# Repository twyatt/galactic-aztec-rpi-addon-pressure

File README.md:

# About

Custom Raspberry Pi Add-on board used as a pressure transducer interface board for the [Galactic Aztec] rocket. The board has a single JST XH port for power input (Supply Voltage), 4 ethernet ports for interfacing with custom [pressure transducer connector boards] and 2 header pin ports (pressure transducer stepped-down voltage output) for optional ribbon cable connectivity.

## Wiring
The ethernet ports adhere to the following [T-568B] wiring configuration:

| Pin | Color        | Function       |
|:---:|:------------:|:--------------:|
| 1   | Orange/White | Signal         |
| 2   | Orange       | Signal         |
| 3   | Green/White  |                |
| 4   | Blue         | Supply Voltage |
| 5   | Blue/White   | Supply Voltage |
| 6   | Green        |                |
| 7   | Brown/White  | Ground         |
| 8   | Brown        | Ground         |

## Launch
For the [Galactic Aztec April 18th, 2015 launch], the following pressure transducers were used:
* 3 x [P51-500-A-A-I36-5V-000-000]
  * LOX, Kerosene and motor pressure
* 1 x [MSP-300-2K5-P-4-N-1]
  * Helium pressure

Custom EagleCAD parts on this board can be found in the [SDSU Rocket Eagle Libraries].

# Bill of Materials
| Qty | Description                               | Part Number       | Vendor   |
|:---:|-------------------------------------------|------------------:|----------|
| 4   | Jack RJ45 CAT5/CAT5e                      | [380-1046-ND]     | DigiKey  |
| 1   | Header JST XH 2.5mm 4-pos Right Angle SMD | [455-2262-1-ND]   | DigiKey  |
| 2   | Header Male 2x5 0.1" Pitch                | [609-3236-ND]     | DigiKey  |
| 4   | Resistor 10kΩ 1/4W 1% 0603                | [P10KBYCT-ND]     | DigiKey  |
| 4   | Resistor 15kΩ 1/4W 1% 0603                | [RHM15.0KADCT-ND] | DigiKey  |
| 1   | Header Stacking 2x20 Tall 23mm            | [1979]            | Adafruit |

[Galactic Aztec]: http://rocket.sdsu.edu/rockets
[pressure transducer connector boards]: https://github.com/twyatt/galactic-aztec-pressure-transducer-connector
[T-568B]: https://en.wikipedia.org/wiki/TIA/EIA-568#Wiring
[Galactic Aztec April 18th, 2015 launch]: https://github.com/twyatt/galactic-aztec-launch-data
[P51-500-A-A-I36-5V-000-000]: http://www.ssi-sensors.com/pdfs/Pressure%20Sensors/P51/PS-AN2_FAMILY%20PRODUCT%20OVERVIEW.pdf
[MSP-300-2K5-P-4-N-1]: http://www.mouser.com/ds/2/418/MSP300-710393.pdf
[SDSU Rocket Eagle Libraries]: https://github.com/twyatt/SDSURocket-Eagle-Libraries
[380-1046-ND]: http://www.digikey.com/product-detail/en/SS-7188-NF/380-1046-ND/388308
[455-2262-1-ND]: http://www.digikey.com/product-detail/en/S4B-XH-SM4-TB(LF)(SN)/455-2262-1-ND/1651060
[609-3236-ND]: http://www.digikey.com/product-detail/en/67997-210HLF/609-3236-ND/1878541
[P10KBYCT-ND]: http://www.digikey.com/product-detail/en/ERJ-PA3F1002V/P10KBYCT-ND/5036115
[RHM15.0KADCT-ND]: http://www.digikey.com/product-detail/en/ESR03EZPF1502/RHM15.0KADCT-ND/1983758
[1979]: https://www.adafruit.com/product/1979

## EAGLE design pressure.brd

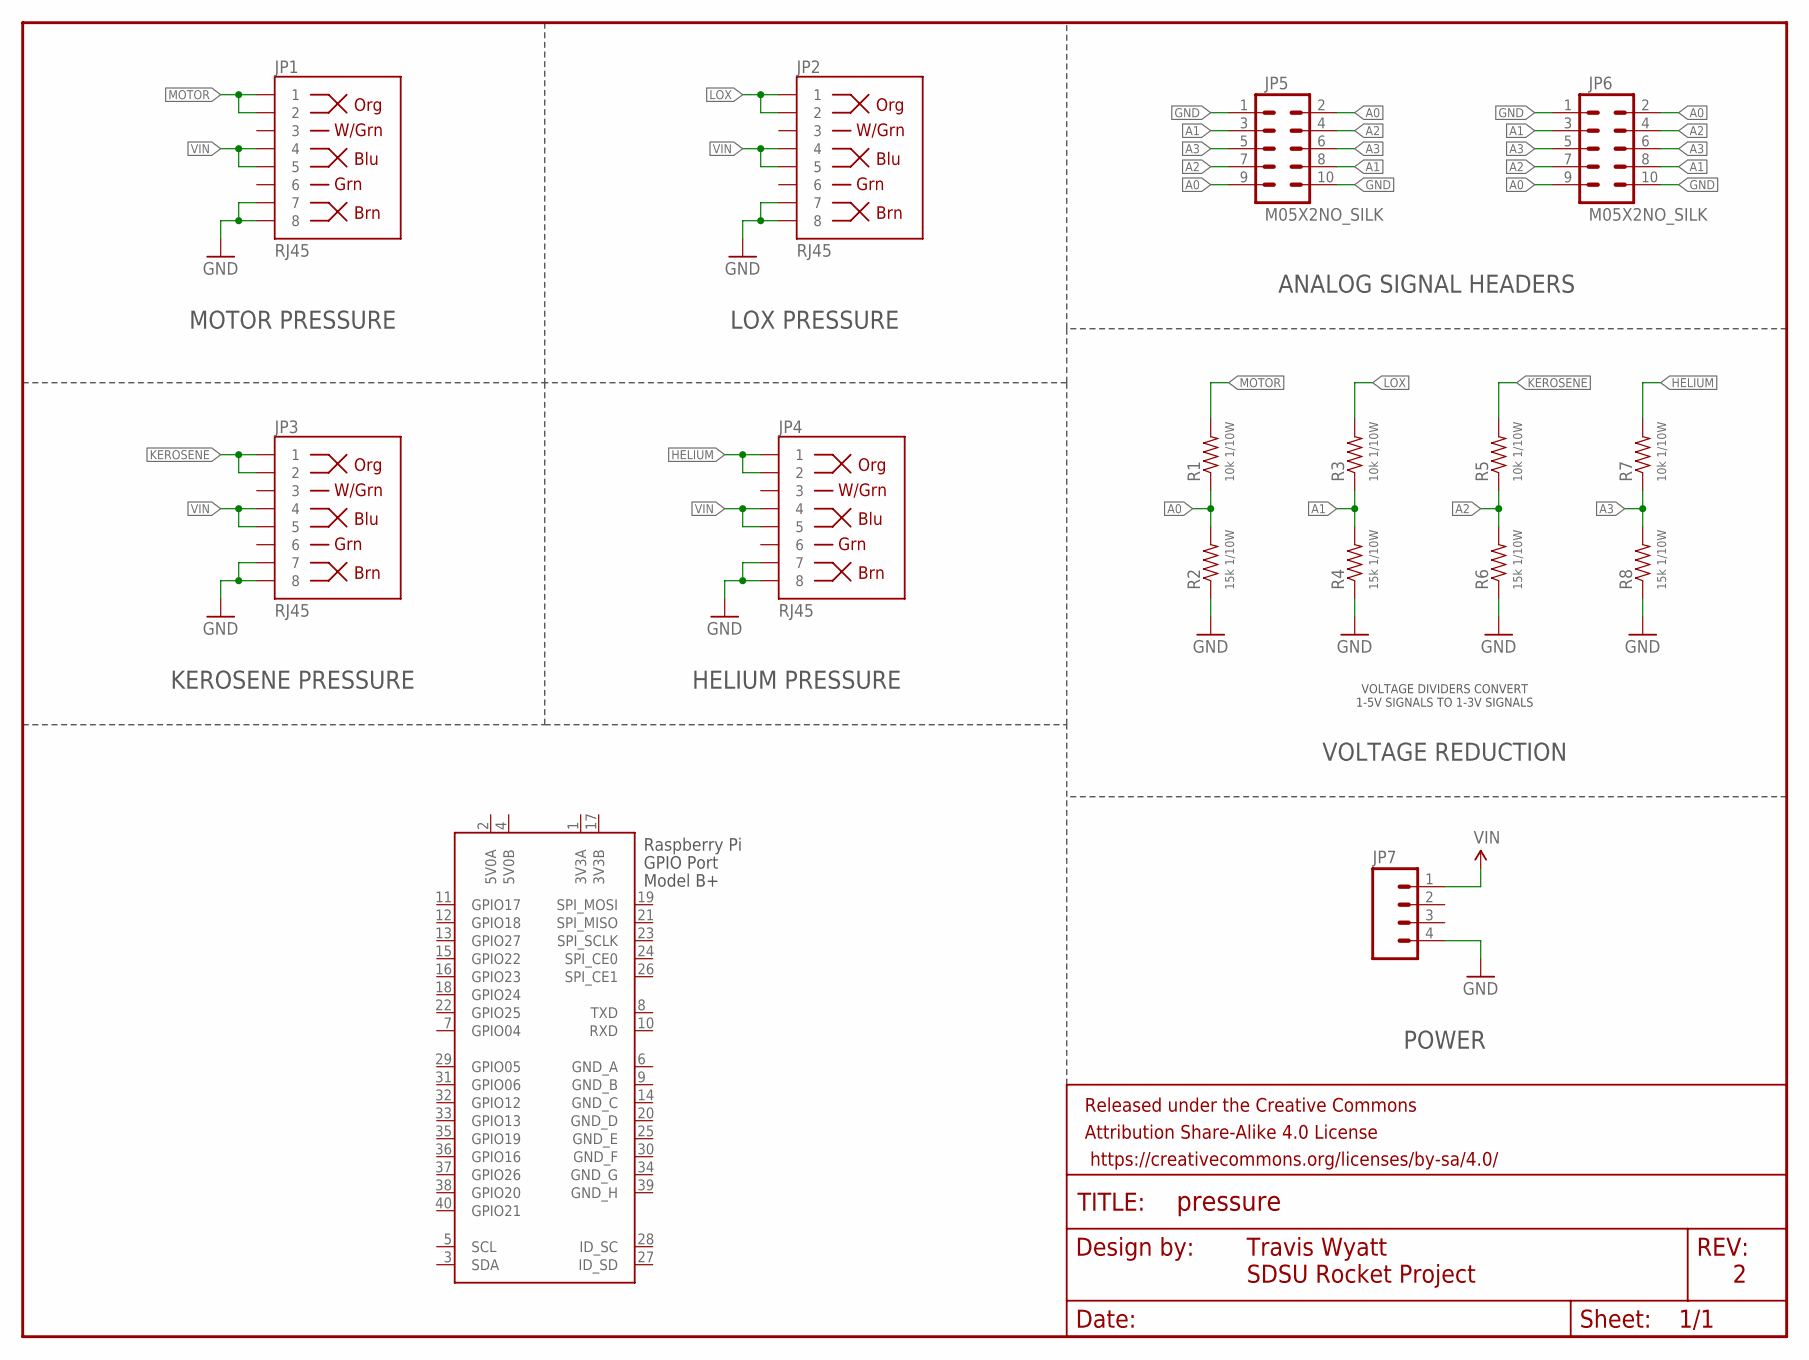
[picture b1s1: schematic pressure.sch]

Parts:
FRAME1: FRAME-LETTER; CREATIVE_COMMONS
JP1, JP2, JP3, JP4: RJ45; RJ45-8
JP5, JP6: M05X2NO_SILK; 2X5_NOSILK
JP7: JST-4POS-2.5MM; S4B-XH-SM4-TB
R1, R3, R5, R7: 10k 1/10W; 0603-RES
R2, R4, R6, R8: 15k 1/10W; 0603-RES
X1: RASPI_BOARD_B+#_H; RASPI_BOARD_B+HAT

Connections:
3V3A: X1.1 (3V3A)
3V3B: X1.17 (3V3B)
5V0A: X1.2 (5V0A)
5V0B: X1.4 (5V0B)
A0: JP5.2, JP5.9, JP6.2, JP6.9, R1.1, R2.2
A1: JP5.3, JP5.8, JP6.3, JP6.8, R3.1, R4.2
A2: JP5.4, JP5.7, JP6.4, JP6.7, R5.1, R6.2
A3: JP5.5, JP5.6, JP6.5, JP6.6, R7.1, R8.2
GND: JP1.7, JP1.8, JP2.7, JP2.8, JP3.7, JP3.8, JP4.7, JP4.8, JP5.1, JP5.10, JP6.1, JP6.10, JP7.4, R2.1, R4.1, R6.1, R8.1
GND_A: X1.6 (GND_A)
GND_B: X1.9 (GND_B)
GND_C: X1.14 (GND_C)
GND_D: X1.20 (GND_D)
GND_E: X1.25 (GND_E)
GND_F: X1.30 (GND_F)
GND_G: X1.34 (GND_G)
GND_H: X1.39 (GND_H)
HELIUM: JP4.1, JP4.2, R7.2
KEROSENE: JP3.1, JP3.2, R5.2
LOX: JP2.1, JP2.2, R3.2
MOTOR: JP1.1, JP1.2, R1.2
VIN: JP1.4, JP1.5, JP2.4, JP2.5, JP3.4, JP3.5, JP4.4, JP4.5, JP7.1

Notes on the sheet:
ANALOG SIGNAL HEADERS
Travis Wyatt
SDSU Rocket Project
MOTOR PRESSURE
KEROSENE PRESSURE
LOX PRESSURE
HELIUM PRESSURE
POWER
VOLTAGE REDUCTION
VOLTAGE DIVIDERS CONVERT 1-5V SIGNALS TO 1-3V SIGNALS

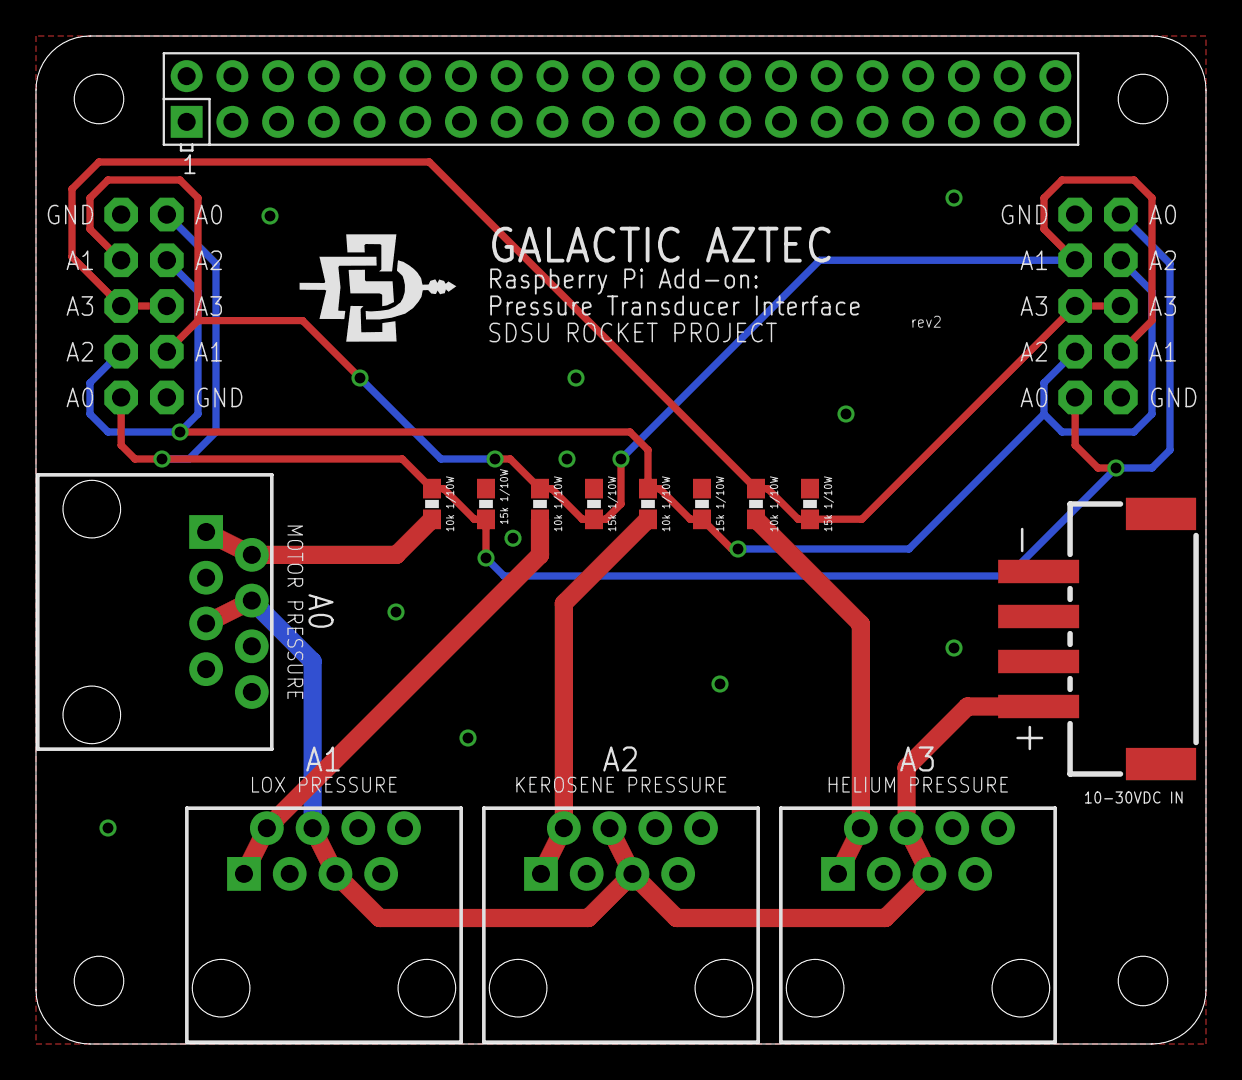
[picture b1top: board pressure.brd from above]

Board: 2 copper layers, 65.0 x 56.0 mm, 17 parts (0 on the bottom side), 10 nets.

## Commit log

2015-07-23 Initial commit.
2015-07-23 Added minor organization headers in README.md.

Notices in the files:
parts and their libraries:
SparkFun-Connectors: Licensing: Creative Commons ShareAlike 4.0 International - https://creativecommons.org/licenses/by-sa/4.0
SparkFun-Aesthetics: Released under the Creative Commons Attribution Share-Alike 4.0 License
SparkFun-Aesthetics: https://creativecommons.org/licenses/by-sa/4.0
